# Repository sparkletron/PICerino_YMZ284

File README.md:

# PICerino YMZ284

Test Board and Software Library for Yamaha YMZ284 sound chips.

author: Jay Convertino  

date: 2024.04.21

license: MIT (software/Hardware)

## Release Versions
### Current
  - release_v1

### Past
  - none
  
## Requirements
### Hardware
  - KiCad
  
### Software
  - xc8 compiler
  
### General Information

Directory Listing:  

  - docs - Data documents for various ICs.
  - schematic - KiCad schematic of YMZ284 test board. See readme.md in dir for details.
  - src - Any source code for the project.
    - lib_picYMZ284 - library with test program for picerino. See readme.md in dir for details.

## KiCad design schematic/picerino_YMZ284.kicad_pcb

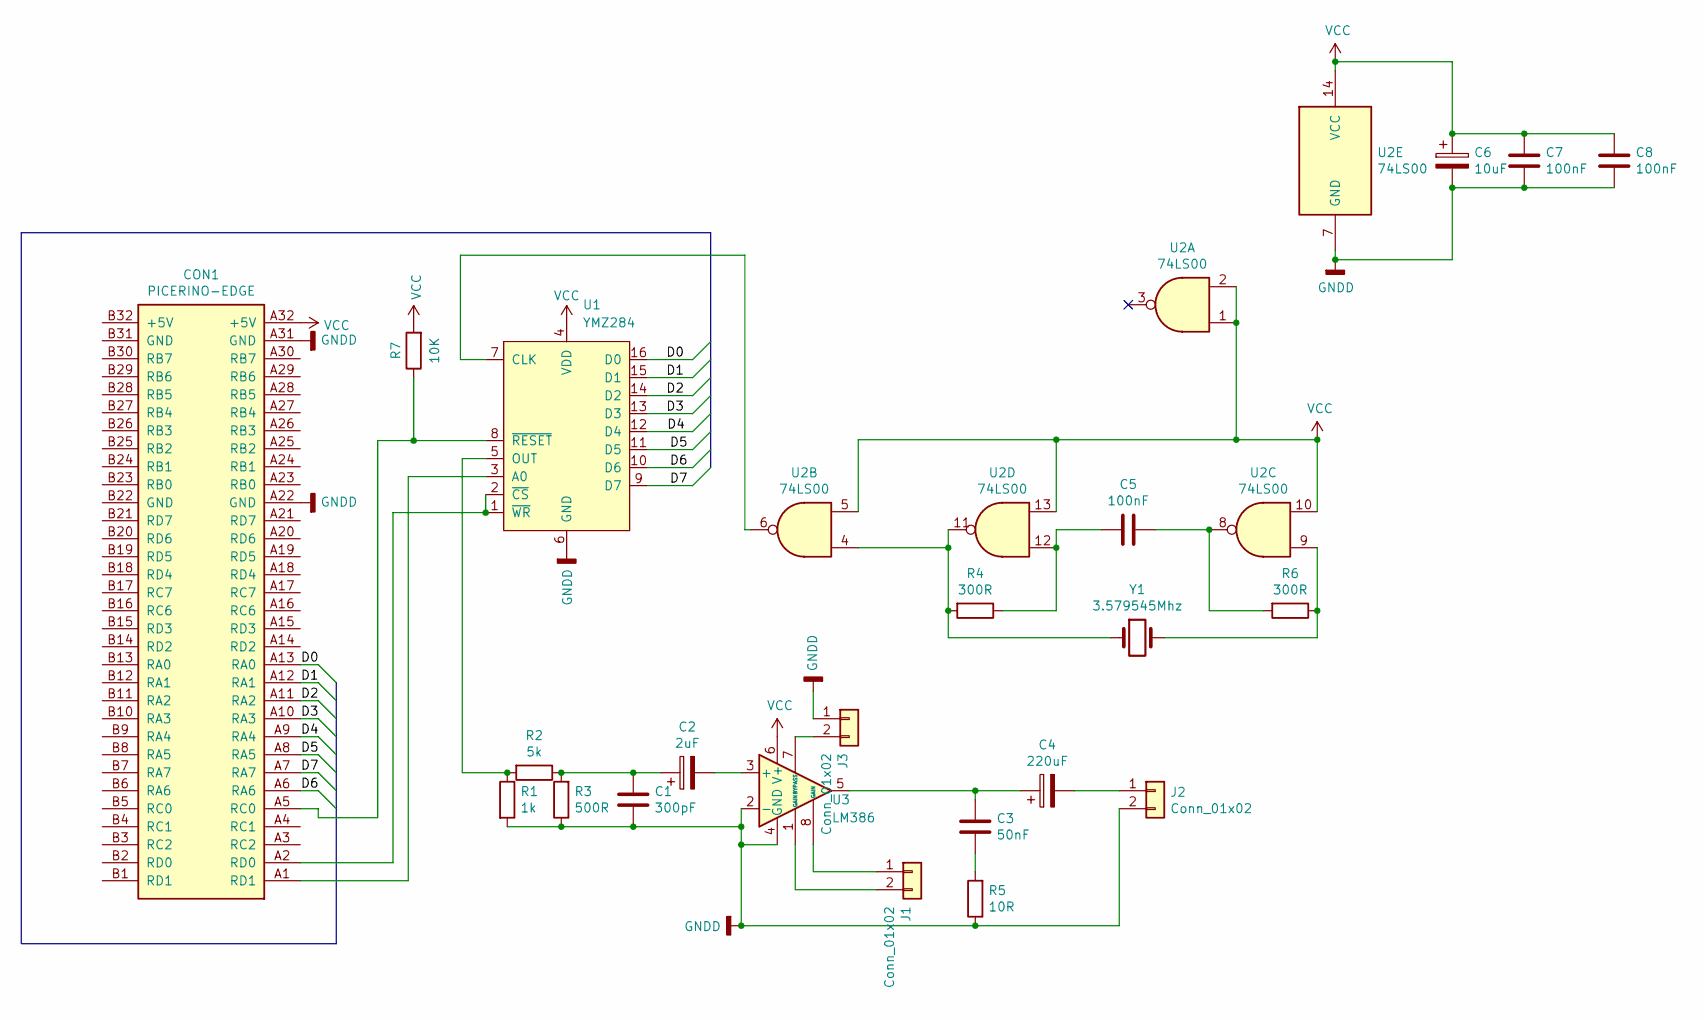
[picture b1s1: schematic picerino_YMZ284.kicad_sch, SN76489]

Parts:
C1: 300pF; C_Disc_D4.7mm_W2.5mm_P5.00mm
C2: 2uF; CP_Radial_D5.0mm_P2.50mm
C3: 50nF; C_Disc_D4.7mm_W2.5mm_P5.00mm
C4: 220uF; CP_Radial_D10.0mm_P5.00mm
C5, C7, C8: 100nF; C_Disc_D4.7mm_W2.5mm_P5.00mm
C6: 10uF; CP_Radial_D5.0mm_P2.50mm
CON1: PICERINO-EDGE; GENESIS-EDGE
J1, J3: Conn_01x02; PinHeader_1x02_P2.54mm_Vertical
J2: Conn_01x02; PhoenixContact_MSTBVA_2,5_2-G_1x02_P5.00mm_Vertical
R1: 1k; R_Axial_DIN0207_L6.3mm_D2.5mm_P7.62mm_Horizontal
R2: 5k; R_Axial_DIN0207_L6.3mm_D2.5mm_P7.62mm_Horizontal
R3: 500R; R_Axial_DIN0207_L6.3mm_D2.5mm_P7.62mm_Horizontal
R4, R6: 300R; R_Axial_DIN0207_L6.3mm_D2.5mm_P7.62mm_Horizontal
R5: 10R; R_Axial_DIN0207_L6.3mm_D2.5mm_P7.62mm_Horizontal
R7: 10K; R_Axial_DIN0207_L6.3mm_D2.5mm_P7.62mm_Horizontal
U1: YMZ284; DIP-16_W7.62mm_LongPads
U2: 74LS00; DIP-14_W7.62mm_LongPads
U3: LM386; DIP-8_W7.62mm_Socket_LongPads
Y1: 3.579545Mhz; Crystal_HC49-U_Vertical

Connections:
/D0: CON1.A13 (RA0), U1.16 (D0)
/D1: CON1.A12 (RA1), U1.15 (D1)
/D2: CON1.A11 (RA2), U1.14 (D2)
/D3: CON1.A10 (RA3), U1.13 (D3)
/D4: CON1.A9 (RA4), U1.12 (D4)
/D5: CON1.A8 (RA5), U1.11 (D5)
/D6: CON1.A6 (RA6), U1.10 (D6)
/D7: CON1.A7 (RA7), U1.9 (D7)
GNDD: C1.1, C6.2, C7.1, C8.1, CON1.A22 (GND), CON1.A31 (GND), J2.2, J3.1, R1.2, R3.1, R5.1, U1.6 (GND), U2.7 (GND), U3.2 (-), U3.4 (GND)
unnamed: C1.2, C2.1, R2.1, R3.2
unnamed: C3.1, R5.2
unnamed: C3.2, C4.1, U3.5
unnamed: C5.1, R6.2, U2.8
unnamed: C5.2, R4.1, U2.12
unnamed: J1.1, U3.8 (GAIN)
unnamed: J1.2, U3.1 (GAIN)
unnamed: C4.2, J2.1
unnamed: J3.2, U3.7 (BYPASS)
unnamed: R4.2, U2.4, U2.11, Y1.1
unnamed: R6.1, U2.9, Y1.2
unnamed: CON1.A1 (RD1), U1.3 (A0)
unnamed: U1.7 (CLK), U2.6
unnamed: R1.1, R2.2, U1.5 (OUT)
unnamed: CON1.A2 (RD0), U1.1 (~WR), U1.2 (~CS)
unnamed: CON1.A5 (RC0), R7.1, U1.8 (~RESET)
unnamed: C2.2, U3.3 (+)
VCC: C6.1, C7.2, C8.2, CON1.A32 (+5V), R7.2, U1.4 (VDD), U2.1, U2.2, U2.5, U2.10, U2.13, U2.14 (VCC), U3.6 (V+)

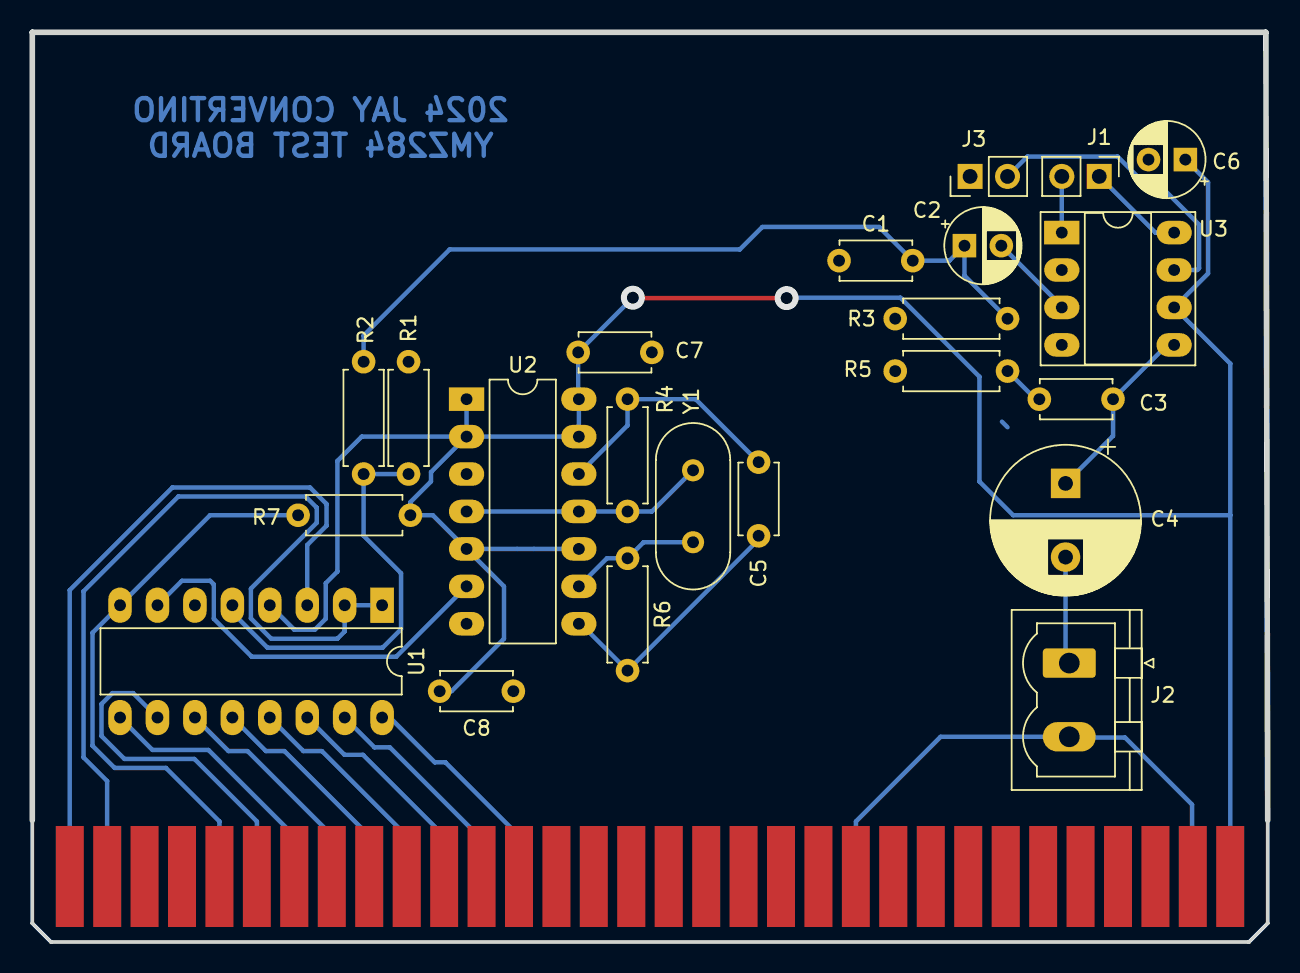
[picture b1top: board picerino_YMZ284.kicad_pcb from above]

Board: 2 copper layers, 83.8 x 61.7 mm, 23 parts (0 on the bottom side), 27 nets.

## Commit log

2022-01-28 fixed bug in io port ansel* setup for D and A ports. Fixed shift amount for reg address (was old from messed up board)
2022-01-28 added bit reversal and changed masking. decision was to keep the bus bits 1 to 1 and reverse in software. performing the opposite for the tms9928 to see which way I prefer. For testing chips it doesn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
2022-01-28 fixed name of noise function
2022-01-28 added code to test all channels in all various modes, seperate at this point.
2022-01-29 updated board to RC port for ready, since RC has pin change interrupts.
2022-01-29 updated kicad schematic and pcb so ready is tied to RC7
2022-01-29 fixed makefile target so it will not regenerate unless files have been updated.
2022-01-29 ready on wrong pin
2022-01-31 moved header file and added doxygen to ignore
2022-01-31 remove library binary
2022-01-31 fixed readme format error
2022-02-13 fixed grammer
2022-02-13 remove returns that were only placeholders for code... totally forgot to remove them... whoops
2022-02-20 reverse bit order on pcb to remove software reversal
2022-02-21 fixed test appliction and simplified library interface
2022-02-21 fixed pcb so bits are reversed as they should be
2022-02-21 added waveforms setup file
2022-02-21 don't add gerbers to repo, update pcb gerber path in kicad
2022-02-23 final tweaks to code, one note... the while loop isn't great for checking the ready. Its too slow, but its universal so using this code on different uC is trivial. Optimize sendData for your applicat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
2022-07-05 updated kicad
2022-11-13 updated schematics to kicad v6
2023-01-16 added mit license
2024-03-25 fixed for github
2024-04-21 first update to YMZ284 from TI sound chip
2024-05-27 first version with library conversion. main test app still needs to be converted
2024-05-27 simple test added, sound channels only
2024-05-28 first working version of channel tests
2024-05-28 remove old ti stuff from readme
